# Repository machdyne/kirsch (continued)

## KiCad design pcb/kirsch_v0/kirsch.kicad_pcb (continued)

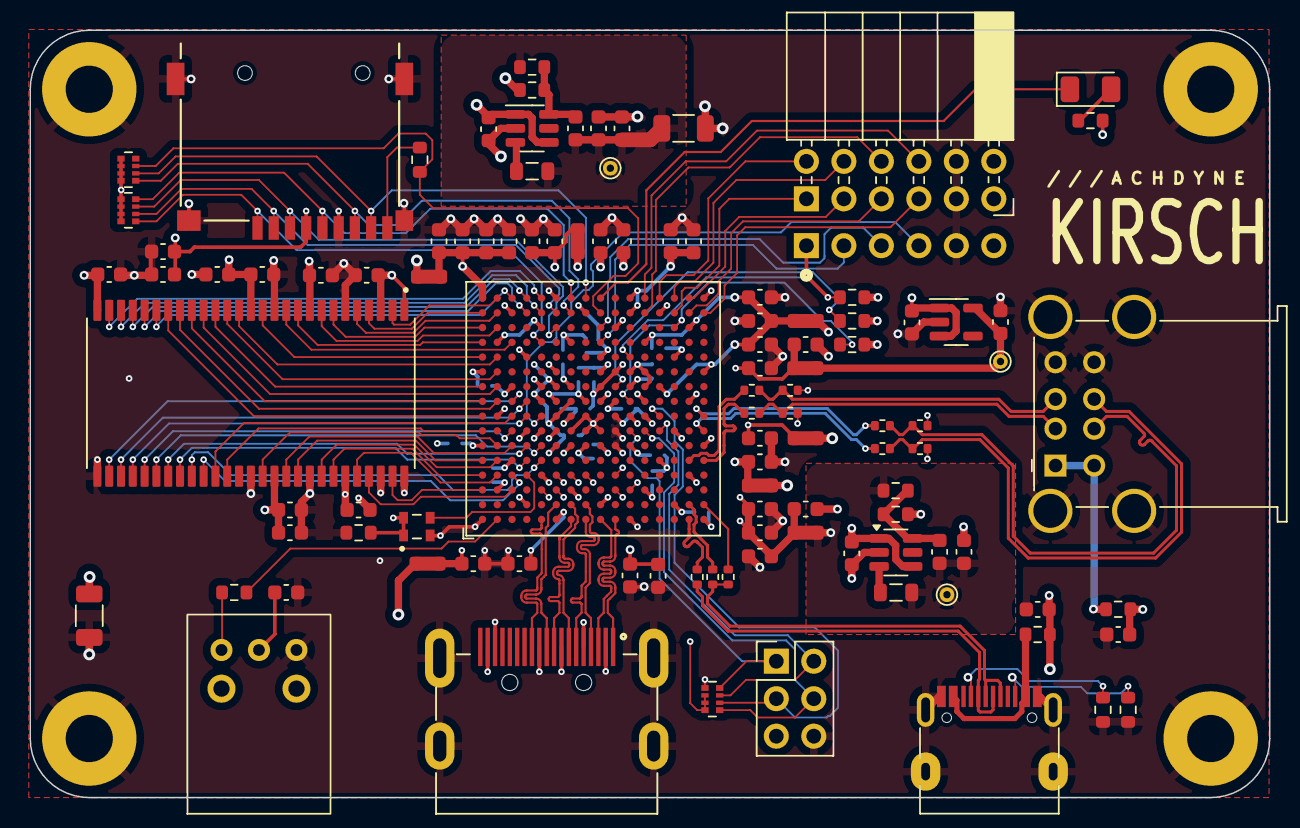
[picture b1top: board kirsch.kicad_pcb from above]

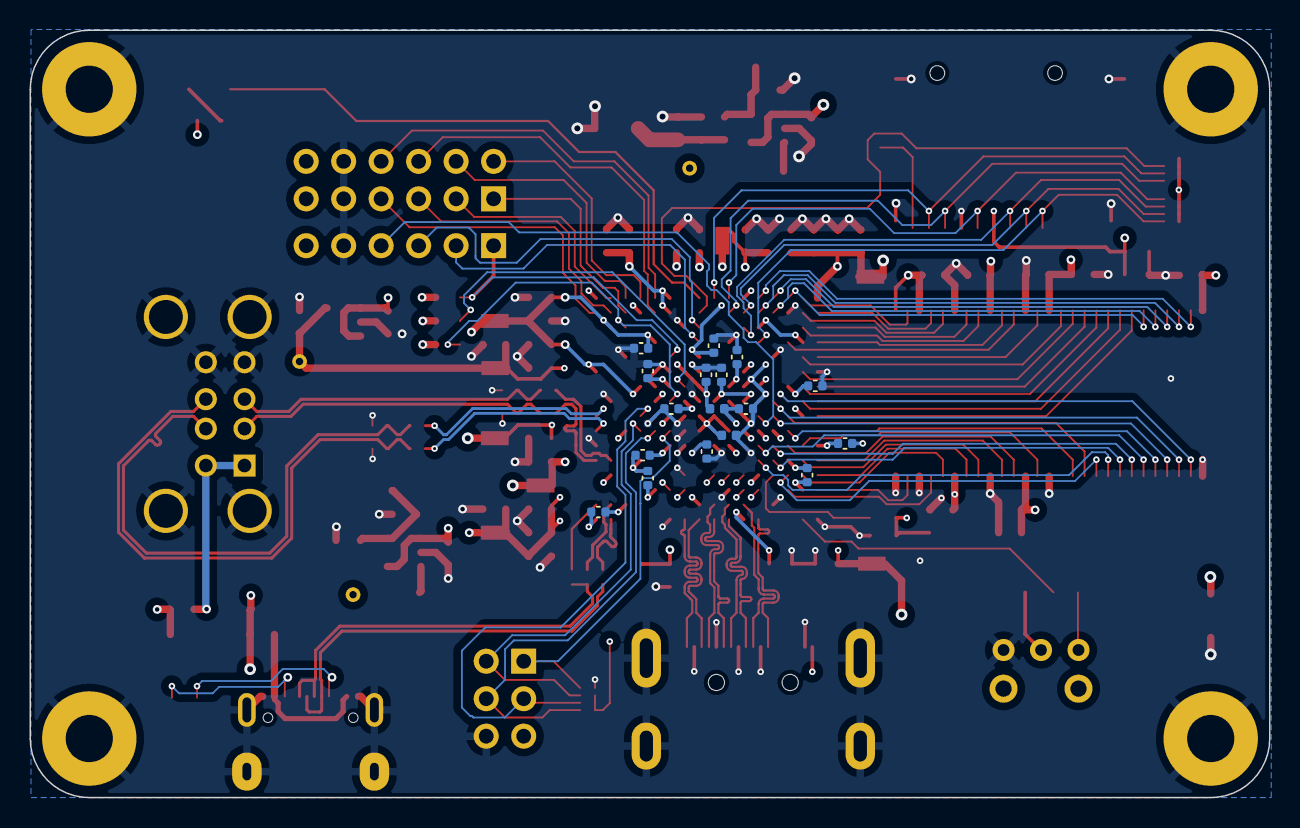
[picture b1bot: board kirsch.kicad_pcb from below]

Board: 4 copper layers, 84.0 x 52.0 mm, 127 parts (17 on the bottom side), 114 nets.

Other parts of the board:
R20: 2K2; R_0603_1608Metric

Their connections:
/CSPI_SS: R20.2; also elsewhere on the board
/PWR3V3: R20.1; also elsewhere on the board

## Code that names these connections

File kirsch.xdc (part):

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# IO constraints
################################################################################
# clk48:0
set_property LOC D4 [get_ports {clk48}]
set_property IOSTANDARD LVCMOS33 [get_ports {clk48}]

# led:0
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set_property IOSTANDARD LVCMOS33 [get_ports {led}]

# sys_rst_n:0
set_property LOC P14 [get_ports {sys_rst_n}]
set_property IOSTANDARD LVCMOS33 [get_ports {sys_rst_n}]

# aud_optical:0
set_property LOC B1 [get_ports {aud_optical}]
set_property IOSTANDARD LVCMOS33 [get_ports {aud_optical}]

# pmod_a1:0
set_property LOC P15 [get_ports {pmod_a1}]
set_property IOSTANDARD LVCMOS33 [get_ports {pmod_a1}]

# pmod_a2:0
set_property LOC R16 [get_ports {pmod_a2}]
set_property IOSTANDARD LVCMOS33 [get_ports {pmod_a2}]

# pmod_a3:0
set_property LOC R15 [get_ports {pmod_a3}]
set_property IOSTANDARD LVCMOS33 [get_ports {pmod_a3}]

# pmod_a4:0
set_property LOC T15 [get_ports {pmod_a4}]
set_property IOSTANDARD LVCMOS33 [get_ports {pmod_a4}]

# pmod_a7:0
set_property LOC N16 [get_ports {pmod_a7}]
set_property IOSTANDARD LVCMOS33 [get_ports {pmod_a7}]

# pmod_a8:0
set_property LOC P16 [get_ports {pmod_a8}]
set_property IOSTANDARD LVCMOS33 [get_ports {pmod_a8}]

# pmod_a9:0
set_property LOC M15 [get_ports {pmod_a9}]
set_property IOSTANDARD LVCMOS33 [get_ports {pmod_a9}]

# pmod_a10:0
set_property LOC M16 [get_ports {pmod_a10}]
set_property IOSTANDARD LVCMOS33 [get_ports {pmod_a10}]

# sdram_clock:0
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
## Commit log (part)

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2024-11-08 add render
2024-11-08 add schematics
2024-11-09 update blinky
2024-11-09 add case
2024-11-09 update case
2024-11-19 add sdroot dtb
2024-11-20 update bitstreams
2025-03-14 add blinky
